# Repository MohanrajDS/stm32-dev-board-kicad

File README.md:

# STM32 Dev Board (KiCad)

A compact 2-layer development board for the **STM32F103C8** (ARM Cortex-M3), designed in **KiCad**. It runs from Micro-USB through an on-board 3.3 V regulator and breaks the MCU pins out to 2.54 mm headers.

| Top | Bottom |
|---|---|
|  |  |

## Hardware

| Item | Detail |
|---|---|
| MCU | STM32F103C8Tx, LQFP-48 (U2) |
| Regulator | AMS1117-3.3, SOT-223 (U1) |
| USB | Micro-USB B, Würth 629105150521 (J4) |
| Clock | 3.2 x 2.5 mm SMD crystal (Y1) with 10 pF load capacitors |
| Switch | SPDT slide switch (SW1) |
| Headers | 3x 1x4 2.54 mm pin headers (J1-J3) |
| Other | Ferrite bead for analog supply filtering, power LED, 0402 decoupling capacitors |
| Layers | 2 |
| Tool | KiCad |

## Repository layout

| File | Description |
|---|---|
| `stm32_trial_.kicad_pro` | KiCad project, open this first |
| `stm32_trial_.kicad_sch` | Schematic |
| `stm32_trial_.kicad_pcb` | PCB layout |
| `629105150521 (rev1).stp` | 3D model of the USB connector |
| `docs/images/` | 3D renders |

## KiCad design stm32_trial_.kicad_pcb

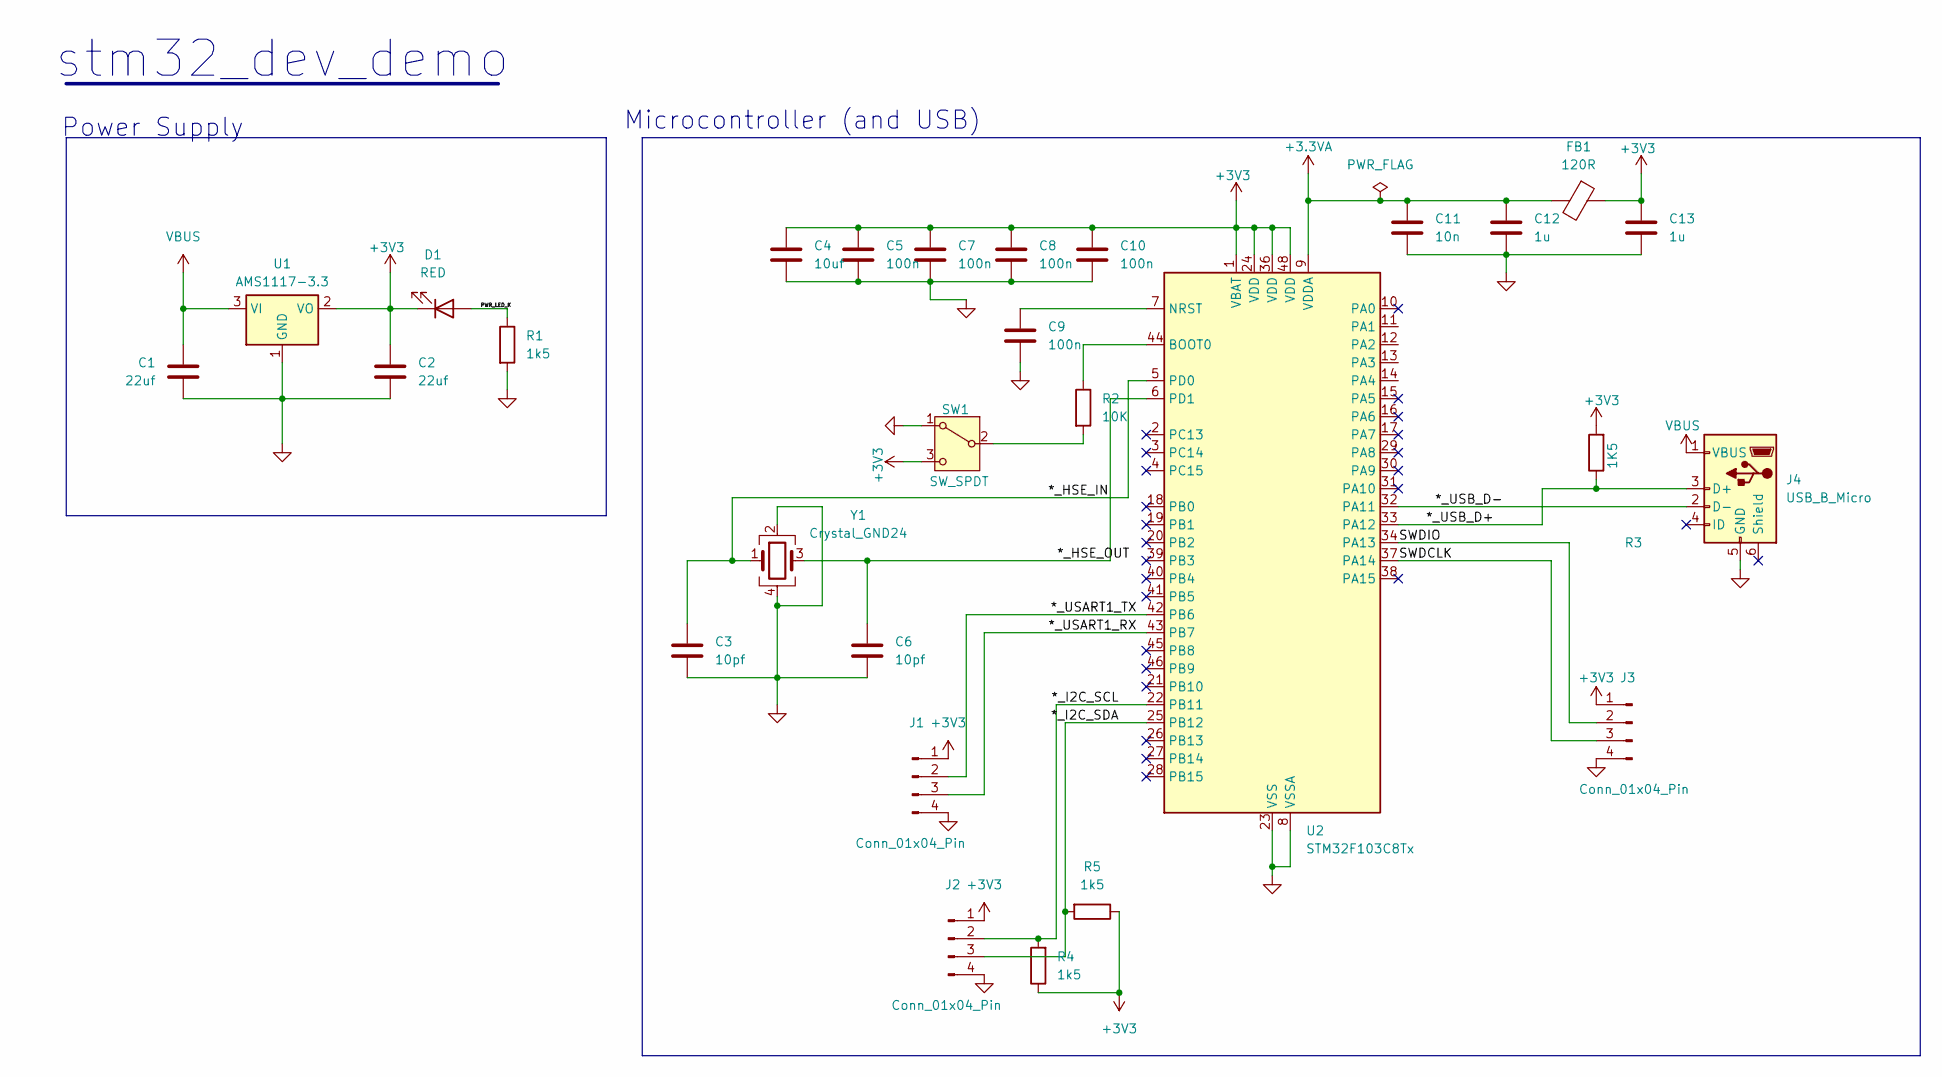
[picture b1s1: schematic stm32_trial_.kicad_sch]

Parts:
C1, C2: 22uf; C_0805_2012Metric
C3, C6: 10pf; C_0402_1005Metric
C4: 10uf; C_0603_1608Metric
C5, C7, C8, C9, C10: 100n; C_0402_1005Metric
C11: 10n; C_0402_1005Metric
C12, C13: 1u; C_0402_1005Metric
D1: RED; LED_0603_1608Metric
FB1: 120R; L_0603_1608Metric
J1, J2, J3: Conn_01x04_Pin; PinHeader_1x04_P2.54mm_Vertical
J4: USB_B_Micro; USB_Micro-B_Wuerth_629105150521
R1, R4, R5: 1k5; R_0402_1005Metric
R2: 10K; R_0402_1005Metric
R3: 1K5; R_0402_1005Metric
SW1: SW_SPDT; SW_SPDT_PCM12
U1: AMS1117-3.3; SOT-223-3_TabPin2
U2: STM32F103C8Tx; LQFP-48_7x7mm_P0.5mm
Y1: Crystal_GND24; Crystal_SMD_3225-4Pin_3.2x2.5mm

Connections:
+3.3VA: C11.1, C12.1, FB1.2, U2.9 (VDDA)
+3V3: C2.1, C4.1, C5.1, C7.1, C8.1, C10.1, C13.1, D1.1 (K), FB1.1, J1.1, J2.1, J3.1, R3.2, R4.1, R5.1, SW1.3 (C), U1.2 (VO), U2.1 (VBAT), U2.24 (VDD), U2.36 (VDD), U2.48 (VDD)
/HSE_IN: C3.1, U2.5 (PD0), Y1.1
/HSE_OUT: C6.1, U2.6 (PD1), Y1.3
/I2C_SCL: J2.2, R4.2, U2.22 (PB11)
/I2C_SDA: J2.3, R5.2, U2.25 (PB12)
/PWR_LED_K: D1.2 (A), R1.1
/SWDCLK: J3.3, U2.37 (PA14)
/SWDIO: J3.2, U2.34 (PA13)
/USART1_RX: J1.3, U2.43 (PB7)
/USART1_TX: J1.2, U2.42 (PB6)
/USB_D+: J4.3 (D+), R3.1, U2.33 (PA12)
/USB_D-: J4.2 (D-), U2.32 (PA11)
GND: C1.2, C2.2, C3.2, C4.2, C5.2, C6.2, C7.2, C8.2, C9.2, C10.2, C11.2, C12.2, C13.2, J1.4, J2.4, J3.4, J4.5 (GND), R1.2, SW1.1 (A), U1.1 (GND), U2.8 (VSSA), U2.23 (VSS), U2.35 (VSS), U2.47 (VSS), Y1.2, Y1.4
unnamed: R2.2, SW1.2 (B)
unnamed: R2.1, U2.44 (BOOT0)
unnamed: C9.1, U2.7 (NRST)
VBUS: C1.1, J4.1 (VBUS), U1.3 (VI)

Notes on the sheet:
Microcontroller (and USB)
Power Supply
stm32_dev_demo

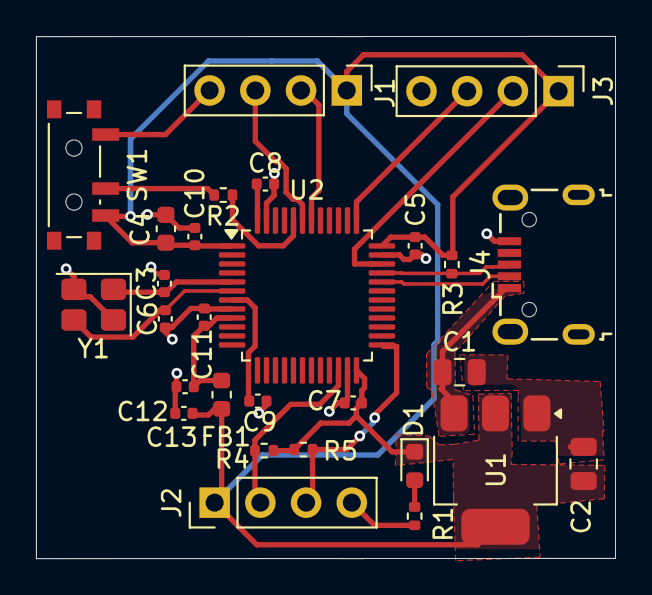
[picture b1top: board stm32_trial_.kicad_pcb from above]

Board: 2 copper layers, 32.2 x 29.0 mm, 28 parts (0 on the bottom side), 18 nets.

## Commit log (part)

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2025-12-19 fixed the issues of unconnected nets
